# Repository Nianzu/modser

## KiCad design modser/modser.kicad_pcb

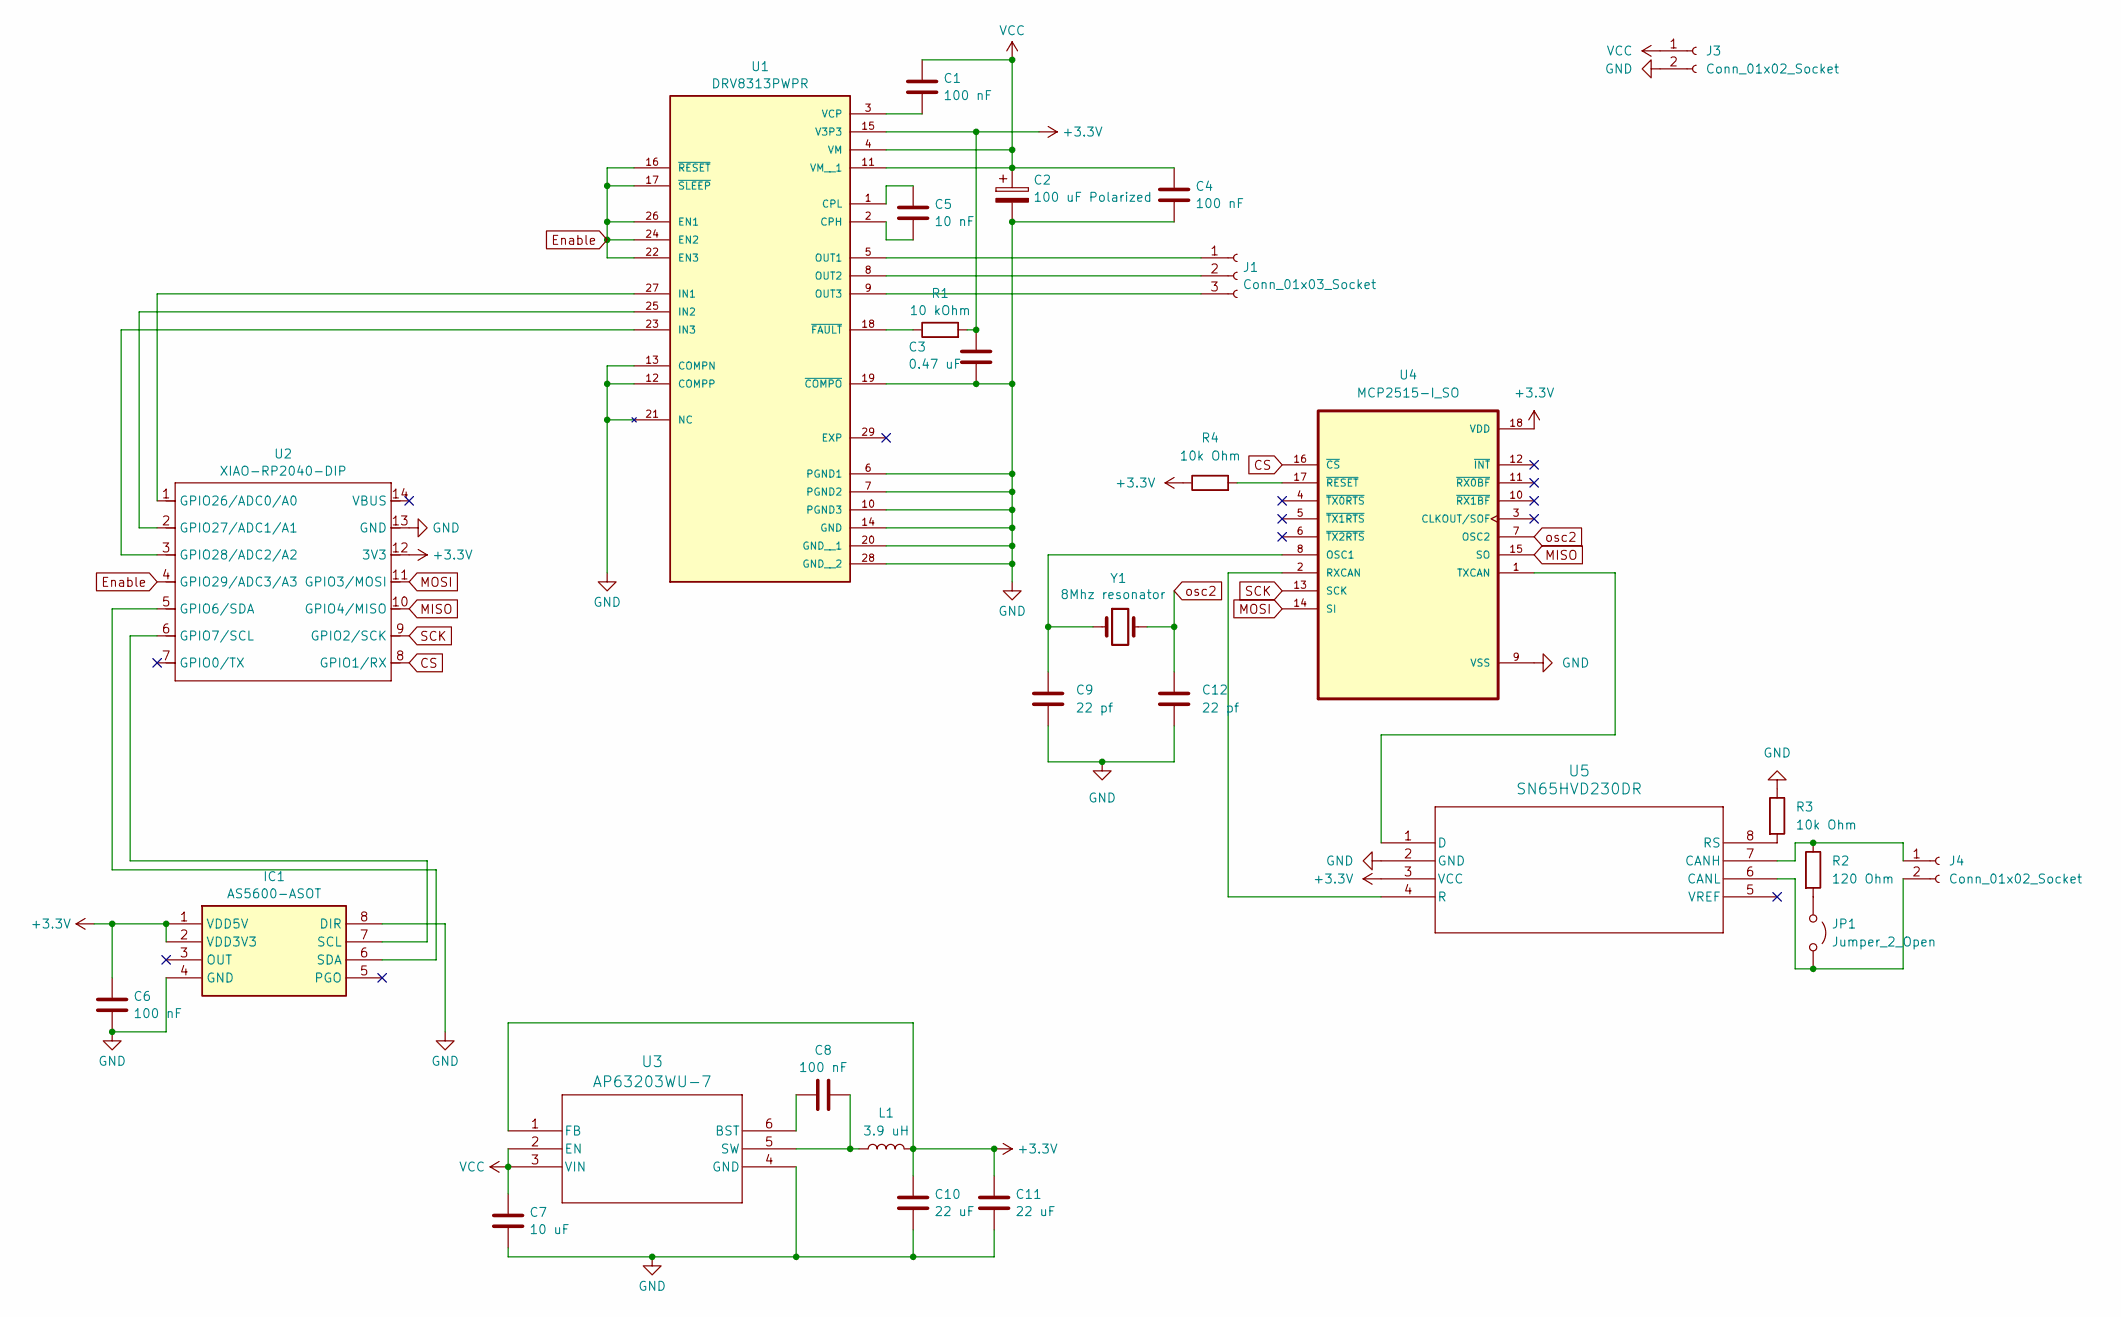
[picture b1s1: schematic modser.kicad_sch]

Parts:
C1, C4, C6, C8: 100 nF; C_0603_1608Metric_Pad1.08x0.95mm_HandSolder
C2: 100 uF Polarized; CAPAE660X800N
C3: 0.47 uF; C_0603_1608Metric_Pad1.08x0.95mm_HandSolder
C5: 10 nF; C_0603_1608Metric_Pad1.08x0.95mm_HandSolder
C7: 10 uF; C_1206_3216Metric
C9, C12: 22 pf; C_0603_1608Metric_Pad1.08x0.95mm_HandSolder
C10, C11: 22 uF; C_1206_3216Metric
IC1: AS5600-ASOT; SOIC127P600X175-8N; Mouser Part Number 985-AS5600-ASOT
J1: Conn_01x03_Socket; PinHeader_1x03_P2.54mm_Vertical
J3, J4: Conn_01x02_Socket; PinHeader_1x02_P2.54mm_Vertical
JP1: Jumper_2_Open; SolderJumper-2_P1.3mm_Bridged_RoundedPad1.0x1.5mm
L1: 3.9 uH; INDC2016X100N
R1: 10 kOhm; R_0603_1608Metric_Pad0.98x0.95mm_HandSolder
R2: 120 Ohm; R_0603_1608Metric_Pad0.98x0.95mm_HandSolder
R3, R4: 10k Ohm; R_0603_1608Metric_Pad0.98x0.95mm_HandSolder
U1: DRV8313PWPR; SOP65P640X120-29N; PARTREV D
U2: XIAO-RP2040-DIP
U3: AP63203WU-7; AP63203WU7
U4: MCP2515-I_SO; SOIC127P1030X265-18N
U5: SN65HVD230DR; D8
Y1: 8Mhz resonator; XTAL_NX3225GD-8MHZ-STD-CRA-3_NDK

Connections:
+3.3V: C3.2, C6.1, C10.1, C11.1, IC1.1 (VDD5V), IC1.2 (VDD3V3), L1.2, R1.2, R4.1, U1.15 (V3P3), U2.12 (3V3), U3.1 (FB), U4.18 (VDD), U5.3 (VCC)
CS: U2.8 (GPIO1/RX), U4.16 (~CS)
Enable: U1.16 (~RESET), U1.17 (~SLEEP), U1.22 (EN3), U1.24 (EN2), U1.26 (EN1), U2.4 (GPIO29/ADC3/A3)
GND: C2.2, C3.1, C4.2, C6.2, C7.2, C9.2, C10.2, C11.2, C12.2, IC1.4 (GND), IC1.8 (DIR), J3.2, R3.1, U1.6 (PGND1), U1.7 (PGND2), U1.10 (PGND3), U1.12 (COMPP), U1.13 (COMPN), U1.14 (GND), U1.19 (~COMPO), U1.20 (GND__1), U1.21 (NC), U1.28 (GND__2), U2.13 (GND), U3.4 (GND), U4.9 (VSS), U5.2 (GND)
MISO: U2.10 (GPIO4/MISO), U4.15 (SO)
MOSI: U2.11 (GPIO3/MOSI), U4.14 (SI)
unnamed: IC1.7 (SCL), U2.6 (GPIO7/SCL)
unnamed: IC1.6 (SDA), U2.5 (GPIO6/SDA)
unnamed: J1.1, U1.5 (OUT1)
unnamed: J1.2, U1.8 (OUT2)
unnamed: J1.3, U1.9 (OUT3)
unnamed: J4.1, R2.1, U5.7 (CANH)
unnamed: J4.2, JP1.2 (B), U5.6 (CANL)
unnamed: JP1.1 (A), R2.2
unnamed: C5.2, U1.2 (CPH)
unnamed: C5.1, U1.1 (CPL)
unnamed: U1.27 (IN1), U2.1 (GPIO26/ADC0/A0)
unnamed: U1.25 (IN2), U2.2 (GPIO27/ADC1/A1)
unnamed: U1.23 (IN3), U2.3 (GPIO28/ADC2/A2)
unnamed: C1.2, U1.3 (VCP)
unnamed: R1.1, U1.18 (~FAULT)
unnamed: C8.1, U3.6 (BST)
unnamed: C8.2, L1.1, U3.5 (SW)
unnamed: C9.1, U4.8 (OSC1), Y1.1
unnamed: U4.2 (RXCAN), U5.4 (R)
unnamed: U4.1 (TXCAN), U5.1 (D)
unnamed: R4.2, U4.17 (~RESET)
unnamed: R3.2, U5.8 (RS)
SCK: U2.9 (GPIO2/SCK), U4.13 (SCK)
VCC: C1.1, C2.1, C4.1, C7.1, J3.1, U1.4 (VM), U1.11 (VM__1), U3.2 (EN), U3.3 (VIN)
osc2: C12.1, U4.7 (OSC2), Y1.2

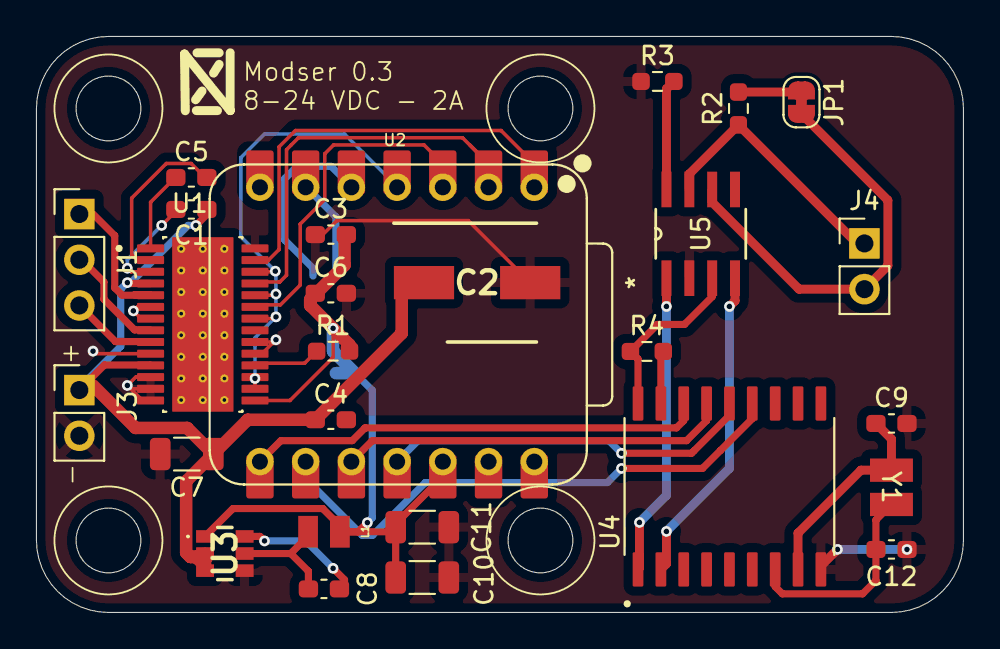
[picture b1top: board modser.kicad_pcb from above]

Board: 2 copper layers, 51.5 x 32.0 mm, 28 parts (1 on the bottom side), 31 nets.

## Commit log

2025-08-05 Got major components with footprints added
2025-08-06 Schematic draft complete!
2025-08-06 Created general outline, speced passives
2025-08-07 Finished layout, working on getting all 3d models added
2025-08-07 Got 3d models for xiao set up
2025-11-05 Fixed issue with design around power regulator
2025-11-05 Able to read angle!
2025-11-06 Fixed issue where reset and sleep lines were never pulled high as required
2025-11-06 Position and torque modes workinggit statusgit status
2025-11-15 Updated schematic with can bus lines
2025-11-26 Sent for production
2025-11-26 Added interactive bom
